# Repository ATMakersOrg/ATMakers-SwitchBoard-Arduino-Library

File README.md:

# ATMakers-SwitchBoard-Arduino-Library
This is a library to control the 5-Relay SwitchBoard from ATMakers.org.

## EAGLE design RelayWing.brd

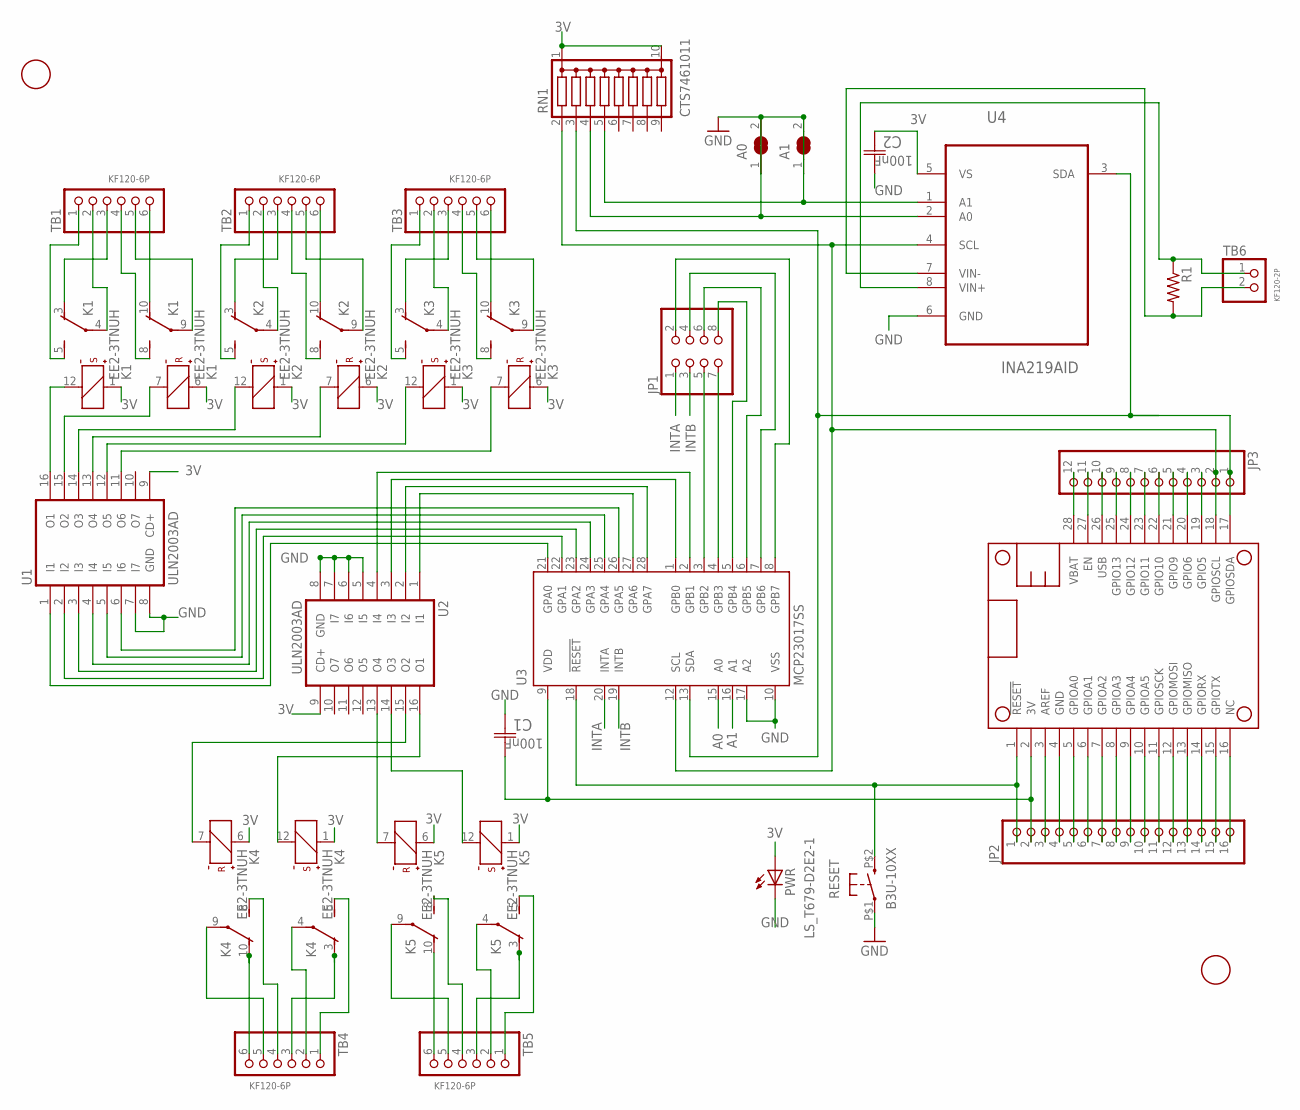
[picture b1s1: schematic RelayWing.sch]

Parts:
A0, A1: SJW
C1, C2: 100nF; CAPC1608X85N
JP1: PINHD-2X4; 2X04
JP2: PINHD-1X16; 1X16
JP3: PINHD-1X12; 1X12
K1, K2, K3, K4, K5: EE2-3TNUH; NUH
MS1: FEATHERWING_NODIM; FEATHERWING_DIM
PWR: LS_T679-D2E2-1; PLCC2
R1: 0.1; M3216
RESET: B3U-10XX
RN1: CTS7461011; CTS746
TB1, TB2, TB3, TB4, TB5: KF120-6P; KF120-6P_ROUND
TB6: KF120-2P; KF120-2P_ROUND
U1, U2: ULN2003AD; SO16
U3: MCP23017SS; SSOP28
U4: INA219AID; SOIC127P600X175-8N
U$2, U$3: FIDUCIAL; FIDUCIAL_1MM

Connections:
3V: C1.1 (C1), C2.2 (C2), JP2.2, K1.1 (+), K1.6 (+), K2.1 (+), K2.6 (+), K3.1 (+), K3.6 (+), K4.1 (+), K4.6 (+), K5.1 (+), K5.6 (+), MS1.2 (3V), PWR.A, RN1.1 (1C), RN1.10 (10C), U1.9 (CD+), U2.9 (CD+), U3.9 (VDD), U4.5 (VS)
A0: A0.1, RN1.4, U3.15 (A0), U4.2 (A0)
A1: A1.1, RN1.5, U3.16 (A1), U4.1 (A1)
GND: A0.2, A1.2, C1.2 (C2), C2.1 (C1), JP2.4, MS1.4 (GND), PWR.C, RESET.P$1, U1.7 (I7), U1.8 (GND), U2.5 (I5), U2.6 (I6), U2.7 (I7), U2.8 (GND), U3.10 (VSS), U3.17 (A2), U4.6 (GND)
GPB2: JP1.5, U3.3 (GPB2)
GPB3: JP1.7, U3.4 (GPB3)
INTA: JP1.1, U3.20 (INTA)
INTB: JP1.3, U3.19 (INTB)
unnamed: JP2.3, MS1.3 (AREF)
unnamed: K4.8 (S), TB4.4
unnamed: JP2.5, MS1.5 (GPIOA0)
unnamed: JP2.6, MS1.6 (GPIOA1)
unnamed: JP2.7, MS1.7 (GPIOA2)
unnamed: JP2.8, MS1.8 (GPIOA3)
unnamed: JP2.9, MS1.9 (GPIOA4)
unnamed: JP2.10, MS1.10 (GPIOA5)
unnamed: JP2.11, MS1.11 (GPIOSCK)
unnamed: JP2.12, MS1.12 (GPIOMOSI)
unnamed: JP2.13, MS1.13 (GPIOMISO)
unnamed: JP2.14, MS1.14 (GPIORX)
unnamed: JP2.15, MS1.15 (GPIOTX)
unnamed: JP2.16, MS1.16 (NC)
unnamed: JP3.3, MS1.19 (GPIO5)
unnamed: K1.5 (S), TB1.1
unnamed: K2.5 (S), TB2.1
unnamed: JP2.1, MS1.1 (!RESET), RESET.P$2 (S), U3.18 (!RESET)
unnamed: JP3.4, MS1.20 (GPIO6)
unnamed: JP3.5, MS1.21 (GPIO9)
unnamed: JP3.6, MS1.22 (GPIO10)
unnamed: JP3.7, MS1.23 (GPIO11)
unnamed: JP3.8, MS1.24 (GPIO12)
unnamed: K1.12 (-), U1.16 (O1)
unnamed: K4.10 (O), TB4.6
unnamed: K2.4, TB2.2
unnamed: K2.3 (O), TB2.3
unnamed: K1.3 (O), TB1.3
unnamed: K1.10 (O), TB1.6
unnamed: K1.4, TB1.2
unnamed: K1.9, TB1.5
unnamed: K2.9, TB2.5
unnamed: K1.7 (-), U1.15 (O2)
unnamed: K1.8 (S), TB1.4
unnamed: K2.12 (-), U1.14 (O3)
unnamed: K2.7 (-), U1.13 (O4)
unnamed: K3.12 (-), U1.12 (O5)
unnamed: K3.7 (-), U1.11 (O6)
unnamed: K4.4, TB4.2
unnamed: K4.5 (S), TB4.1
unnamed: K5.4, TB5.2
unnamed: K5.5 (S), TB5.1
unnamed: K5.10 (O), TB5.6
unnamed: K5.9, TB5.5
unnamed: K5.8 (S), TB5.4
unnamed: K4.9, TB4.5
unnamed: K5.3 (O), TB5.3
unnamed: JP3.9, MS1.25 (GPIO13)
unnamed: K3.5 (S), TB3.1
unnamed: K3.3 (O), TB3.3
unnamed: K3.4, TB3.2
unnamed: K3.8 (S), TB3.4
unnamed: K3.10 (O), TB3.6
unnamed: K3.9, TB3.5
unnamed: K4.12 (-), U2.16 (O1)
unnamed: K4.7 (-), U2.15 (O2)
unnamed: K5.12 (-), U2.14 (O3)
unnamed: JP3.11, MS1.27 (EN)
unnamed: U1.1 (I1), U3.21 (GPA0)
unnamed: U1.2 (I2), U3.22 (GPA1)
unnamed: U1.3 (I3), U3.23 (GPA2)
unnamed: U1.5 (I5), U3.25 (GPA4)
unnamed: U1.6 (I6), U3.26 (GPA5)
unnamed: U1.4 (I4), U3.24 (GPA3)
unnamed: U2.1 (I1), U3.27 (GPA6)
unnamed: U2.2 (I2), U3.28 (GPA7)
unnamed: U2.3 (I3), U3.1 (GPB0)
unnamed: U2.4 (I4), U3.2 (GPB1)
unnamed: K2.8 (S), TB2.4
unnamed: K5.7 (-), U2.13 (O4)
unnamed: JP1.8, U3.5 (GPB4)
unnamed: JP1.6, U3.6 (GPB5)
unnamed: JP1.4, U3.7 (GPB6)
unnamed: JP1.2, U3.8 (GPB7)
unnamed: K2.10 (O), TB2.6
unnamed: K4.3 (O), TB4.3
SCL: JP3.2, MS1.18 (GPIOSCL), RN1.2, U3.12 (SCL), U4.4 (SCL)
SDA: JP3.1, MS1.17 (GPIOSDA), RN1.3, U3.13 (SDA), U4.3 (SDA)
USB: JP3.10, MS1.26 (USB)
VBAT: JP3.12, MS1.28 (VBAT)
VIN+: R1.1, TB6.1, U4.8 (VIN+)
VIN-: R1.2, TB6.2, U4.7 (VIN-)

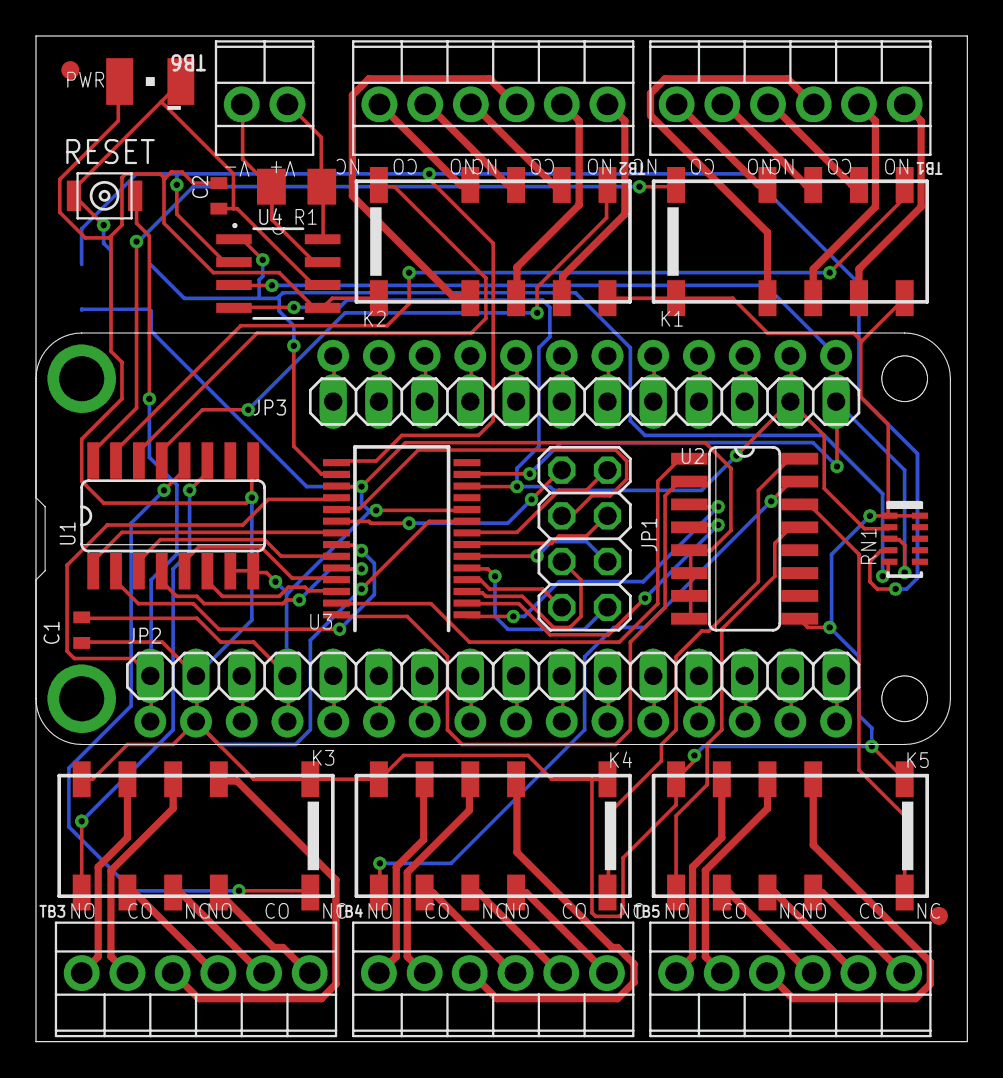
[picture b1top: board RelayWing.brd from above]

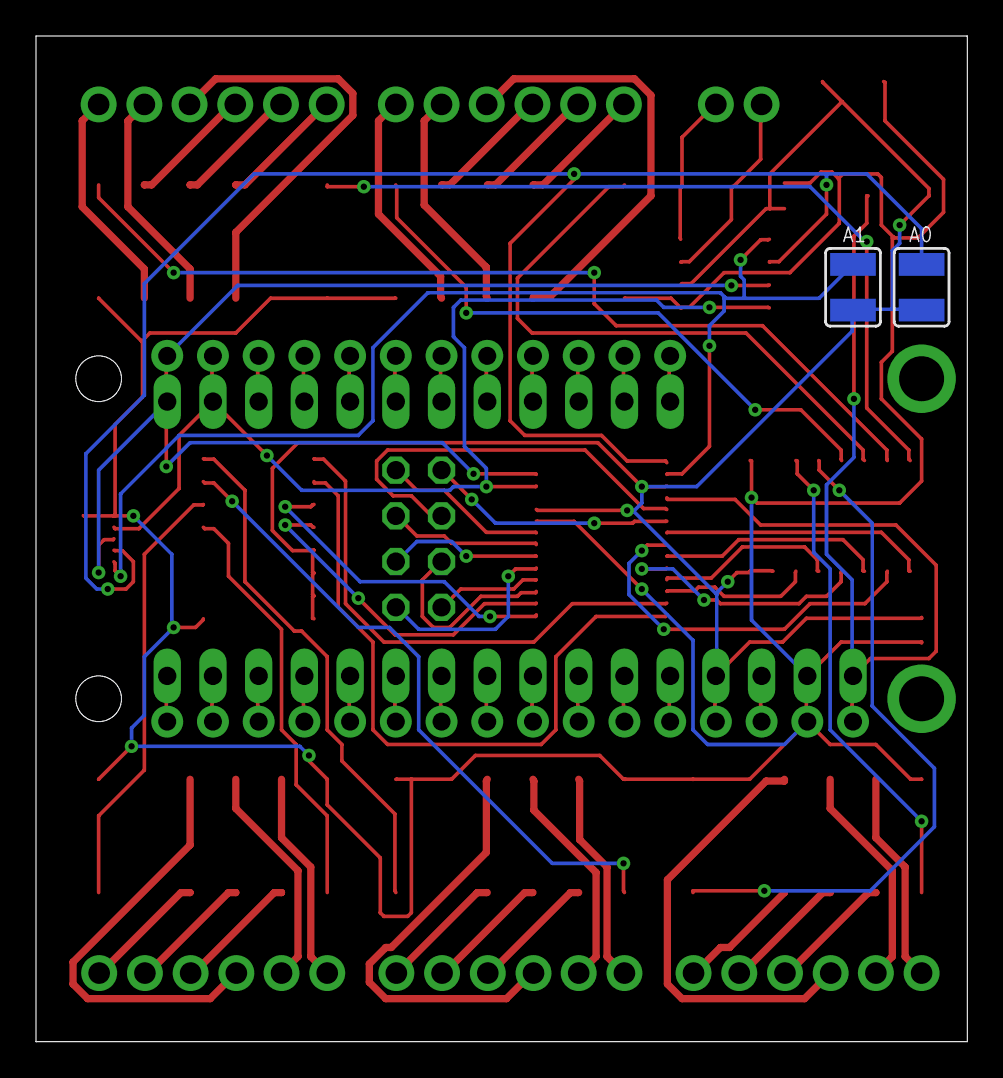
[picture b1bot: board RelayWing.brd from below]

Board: 2 copper layers, 51.7 x 55.9 mm, 29 parts (2 on the bottom side), 90 nets.

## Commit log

2018-03-08 Add files via upload
    Components done. Topside labeling done. Using Eagle 8.6.3
2018-03-09 Moving to Hardware
2018-03-09 wrong repo - removing
2018-03-10 Initial Draft
    This is a first stab at the library. Just the header really - if the inheritance works like I expect, this should be pretty simple with it just inheriting from the MCP23017 and the INA219 (since it h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
2018-03-10 Stupid fix to pull out the time delay
2018-06-05 First rewrite
    Switch from multiple inheritance to just encapsulation - much simpler and easier to control.
    Current Sensor not yet implemented.
2018-07-15 Adding tester code
2018-07-29 Wrapped INA, c'tor, report.
2018-07-30 Obj to struct, passed by ref.
    New names for data struture and method. Struct passed by reference. No printing. Accessors for current threshold. No parameter for csActivity().
    Removed FIXMEs.
2018-07-30 Removed unused Streaming.h
2018-07-30 Adding SwitchRouter2x3 example
2018-07-31 Fixed cs addr, keywords, typo,
2018-08-03 Move example sketch to its own folder
    The Arduino IDE opens all files from a sketch folder as tabs of one project. So multiple sketches in the same folder causes compilation to fail with "redefinition of" errors.
2018-08-14 Adding good SwitchRouter 2x3 Examples
2018-08-28 Works with Adafruit_INA219 lib ver 1.03
    New version of INA219 has different begin() args. This mod to our begin() will initialize the INA219 differently if the new library is detected.
2018-09-04 Published to match Jim Lubin's
2018-09-09 Correct misspelled keywords.txt KEYWORD_TOKENTYPE
    HEYWORD2 -> KEYWORD2
2018-09-09 Use a single tab field separator in keywords.txt
    Each field of keywords.txt is separated by a single true tab. When you use multiple tabs it causes the field to be interpreted as empty. On Arduino IDE 1.6.5 and newer an empty KEYWORD_TOKENTYPE caus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
    Reference:
    https://github.com/arduino/Arduino/wiki/Arduino-IDE-1.5:-Library-specification#keywords
